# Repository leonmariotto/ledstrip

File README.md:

# Led Strip Project !

The goal here is to make a led strip controller board that just work.
Among other things the controller include a 3S battery and 4 potentiometer to control
RGBW independently.

The project layout is :
- hardware: kicad project to make the led strip controller board. Use KiCAD 9.
- cad: printable case for the controller + battery.
- software: software used to control the led strip. 
- ai: a setup to run CLI agent (codex) inside a docker with support for multiple AGENTS.md and support for KiMCP server.
- tools: tool to assist during development. Include KiMCP submodule.

## System requirements

- Must have a on/off switch
- Must have a battery properly scaled.
- Must provide a way to control color independently.
- Leds must be RGB with controllable intensity.
- Must provide a way to charge battery
- Must provide a way to program internal flash of MCU.
- Must be enclosed by a case.

## First board

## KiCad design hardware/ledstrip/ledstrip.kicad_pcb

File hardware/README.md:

# Hardware design for led strip controller !

## Hardware Requirements

- Must have a on/off switch
- Must provide a USB-C socket
- Must use a serie of Li-Ion battery along with a BMS
- Must use USB-C Power Delivery feature for efficient charging.
- Must use one potentiometer to control one color.
- Must provide an easy access to log via USB.
- Must support run while charging battery.
- Must provide protections against heating and short circuit.

## Ledstrip part !

Choosen RGBW ledstrip of 2 meters.
https://opencircuit.fr/produit/analog-rgbw-led-strip-rgb-plus-warm-white-60

## Hardware Architecture Design

So far the following components is identified :
- 3S Li-ion battery pack. 12V output.
- 3S BMS: off the shelf 3S (3-cells) BMS module. Shall support currents >
to expected (for 2 meter strip the expected current is 3.2A at 12V. So design it to 5-10A.
Start with an external BMS module, then progressively move into an integrated
BMS.
- USB-C connector
- USB to UART bridge (Silicon Labs CP2102(N), or FTDI FT230x or CH340)
- USB Power Delivery controller (ST STUSB4500) used to negociate high power input from USB.
- Battery charger IC (BQ25703A) : accept PD voltage and implement CC/CV.
Provide support for system load while charging.
- Buck regulator (12V to 3.3V) : integrated converter IC
- Logic-level N-MOSFETS x3, low RDS(on).
- Gate resistor / gate pull-down for each MOSFET, Fuse, ESD protections (TVS diodes, Schottky),
- Dedicated MIPI-10 connector for SWD.
- STM32G030K6 MCU.

### STM32G030K6 32-bit LQFP package

Use the following wiring :
- SWD: PA13, PA14, NRST
- UART: PA9 (TX), PA10 (RX)
- ADC (pots): PA0, PA1, PA2
- I2C to BQ25703A: PB6 (SCL), PB7 (SDA)
- PWM to MOSFET: PA8, PA6, PA7
- Power pins: VDD, VDDA, VSS, VSSA (decouple properly)
- BQ25703A_PROCHOT: PB9
- BQ25703A_CHRG_OK: PB9
Note that PWM need to use TIM1 for PA0 and TIM3 for PA6 and PA7 due to conflicts with UART.

## Building

A CI is here to build Gerber on a stable and reproducible environment.
PCBway is the recommended manufacturer.

## 4 layers

- Top (F.Cu): components + most routing (especially short local routes)
- Inner 1: solid GND plane (no splits)
- Inner 2: power pours (3.3 V, 12 V) + only necessary routing (prefer short, controlled routes)
- Bottom (B.Cu): routing + GND pour (stitched to Inner 1 often); use power pours only where it clearly helps (short distribution or local planes)

# TODO

- Create missing 3D view for footprint that lack it.
- MPN (Manufacturer Part Number) shall be included in the CI's BOM
- Generate Pick & Place (CPL/XY)
- Generate Plot Assembly Drwaing (Top/Bottom)

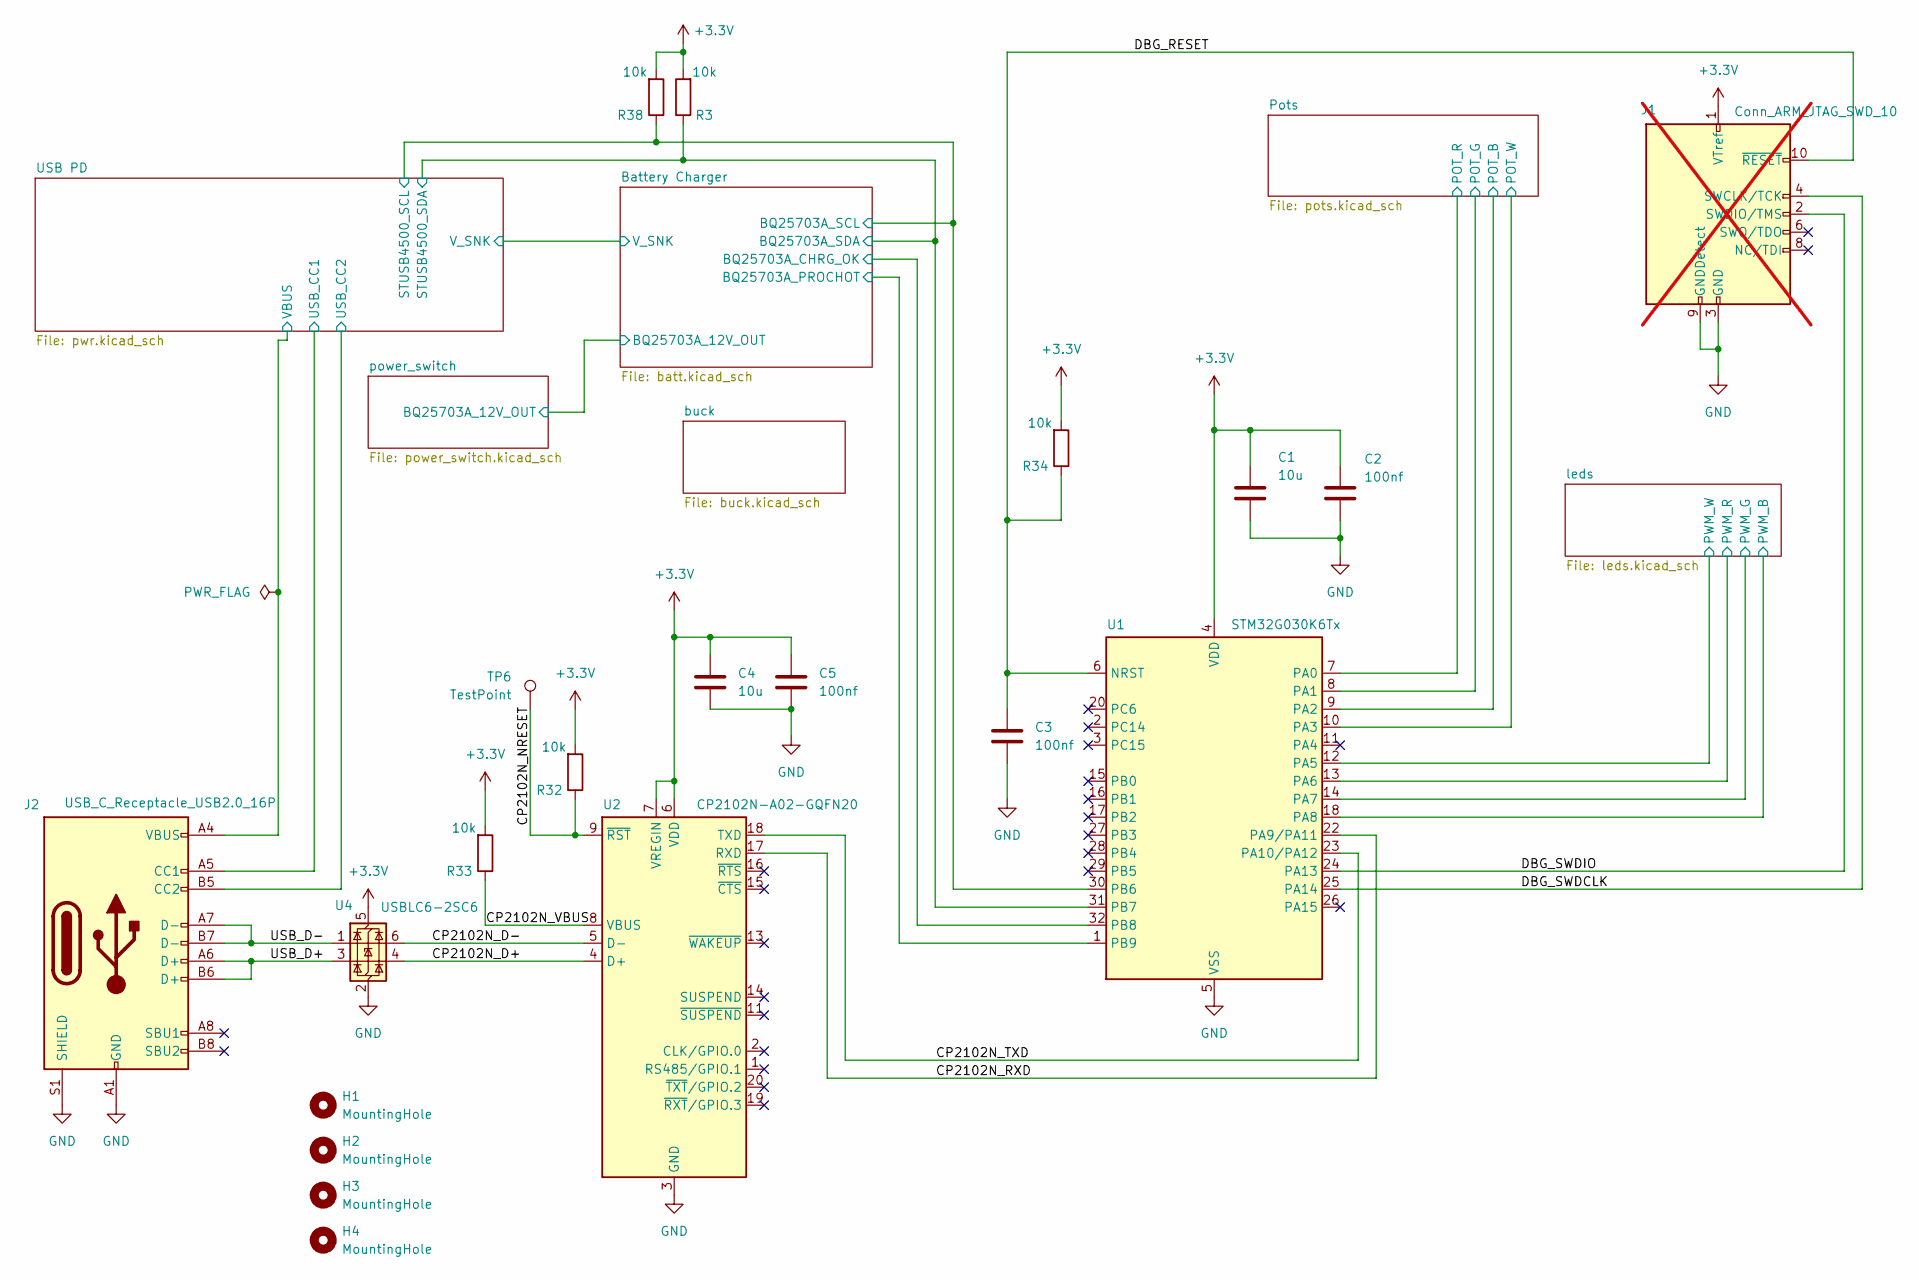
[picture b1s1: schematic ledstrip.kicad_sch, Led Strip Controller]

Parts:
C1, C4: 10u; C_0805_2012Metric; MPN CL21A106KAYNNN
C2, C3, C5: 100nf; C_0603_1608Metric; MPN CL10B104KA8VPJC
H1, H2, H3, H4: MountingHole; MountingHole_3.2mm_M3
J1: Conn_ARM_JTAG_SWD_10; PinHeader_2x05_P1.27mm_Vertical; not fitted
J2: USB_C_Receptacle_USB2.0_16P; USB_C_Receptacle_GCT_USB4105-xx-A_16P_TopMnt_Horizontal_PRO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; MPN USB4105-GF-A-060
R3, R32, R33, R34, R38: 10k; R_0805_2012Metric; MPN MCU0805MD1002BP500
TP6: TestPoint; TestPoint_Pad_1.0x1.0mm
U1: STM32G030K6Tx; LQFP-32_7x7mm_P0.8mm; MPN STM32G030K6T6
U2: CP2102N-A02-GQFN20; SiliconLabs_QFN-20-1EP_3x3mm_P0.5mm_EP1.8x1.8mm; MPN CP2102N-A02-GQFN20
U4: USBLC6-2SC6; SOT-23-6; MPN USBLC6-2SC6

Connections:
+3.3V: C1.1, C2.1, C4.1, C5.1, J1.1 (VTref), R3.2, R32.2, R33.2, R34.2, R38.2, U1.4 (VDD), U2.6 (VDD), U2.7 (VREGIN), U4.5 (VBUS); also elsewhere on the board
/Battery Charger/BQ25703A_CHRG_OK: U1.32 (PB8); also elsewhere on the board
/Battery Charger/BQ25703A_PROCHOT: U1.1 (PB9); also elsewhere on the board
/Battery Charger/BQ25703A_SCL: R38.1, U1.30 (PB6); also elsewhere on the board
/Battery Charger/BQ25703A_SDA: R3.1, U1.31 (PB7); also elsewhere on the board
/CP2102N_D+: U2.4 (D+), U4.4 (I/O2)
/CP2102N_D-: U2.5 (D-), U4.6 (I/O1)
/CP2102N_NRESET: R32.1, TP6.1, U2.9 (~RST)
/CP2102N_RXD: U1.22 (PA9/PA11), U2.17 (RXD)
/CP2102N_TXD: U1.23 (PA10/PA12), U2.18 (TXD)
/CP2102N_VBUS: R33.1, U2.8 (VBUS)
/DBG_RESET: C3.1, J1.10 (~RESET), R34.1, U1.6 (NRST)
/DBG_SWDCLK: J1.4 (SWCLK/TCK), U1.25 (PA14)
/DBG_SWDIO: J1.2 (SWDIO/TMS), U1.24 (PA13)
/Pots/POT_B: U1.9 (PA2); also elsewhere on the board
/Pots/POT_G: U1.8 (PA1); also elsewhere on the board
/Pots/POT_R: U1.7 (PA0); also elsewhere on the board
/Pots/POT_W: U1.10 (PA3); also elsewhere on the board
/USB PD/USB_CC1: J2.A5 (CC1); also elsewhere on the board
/USB PD/USB_CC2: J2.B5 (CC2); also elsewhere on the board
/USB PD/VBUS: J2.A4 (VBUS), J2.A9 (VBUS), J2.B4 (VBUS), J2.B9 (VBUS); also elsewhere on the board
/USB_D+: J2.A6 (D+), J2.B6 (D+), U4.3 (I/O2)
/USB_D-: J2.A7 (D-), J2.B7 (D-), U4.1 (I/O1)
/leds/PWM_B: U1.18 (PA8); also elsewhere on the board
/leds/PWM_G: U1.14 (PA7); also elsewhere on the board
/leds/PWM_R: U1.13 (PA6); also elsewhere on the board
/leds/PWM_W: U1.12 (PA5); also elsewhere on the board
GND: C1.2, C2.2, C3.2, C4.2, C5.2, J1.3 (GND), J1.5 (GND), J1.9 (GNDDetect), J2.A1 (GND), J2.A12 (GND), J2.B1 (GND), J2.B12 (GND), J2.S1 (SHIELD), U1.5 (VSS), U2.3 (GND), U2.12 (GND), U2.21 (GND), U4.2 (GND); also elsewhere on the board

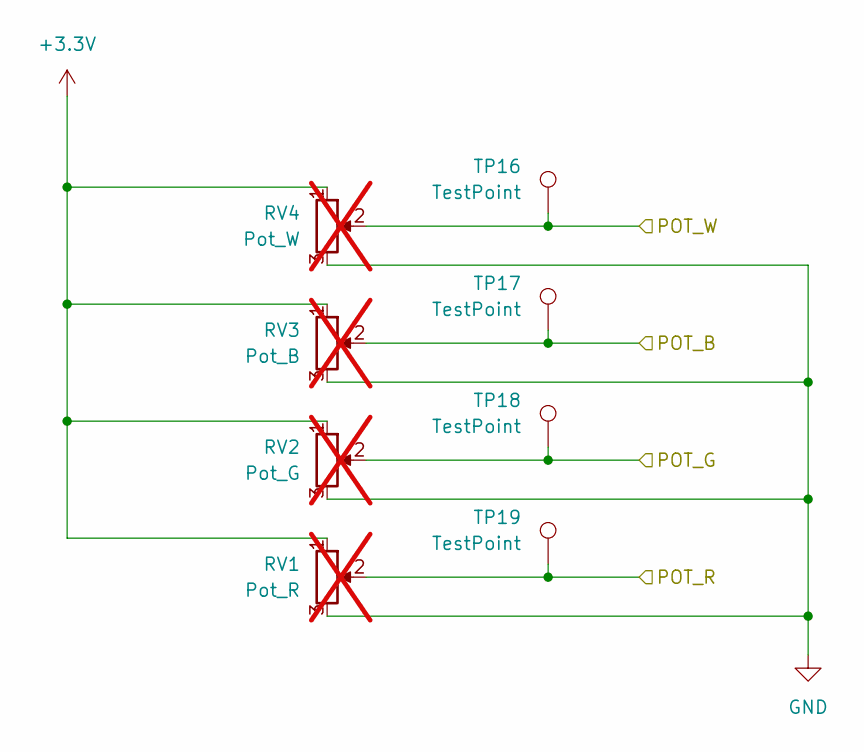
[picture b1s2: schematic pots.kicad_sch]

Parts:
RV1: Pot_R; Potentiometer_Bourns_PTV09A-1_Single_Vertical; MPN PTV09A-6030U-B103; not fitted
RV2: Pot_G; Potentiometer_Bourns_PTV09A-1_Single_Vertical; MPN PTV09A-6030U-B103; not fitted
RV3: Pot_B; Potentiometer_Bourns_PTV09A-1_Single_Vertical; MPN PTV09A-6030U-B103; not fitted
RV4: Pot_W; Potentiometer_Bourns_PTV09A-1_Single_Vertical; MPN PTV09A-6030U-B103; not fitted
TP16, TP17, TP18, TP19: TestPoint; TestPoint_Pad_1.0x1.0mm

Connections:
+3.3V: RV1.1, RV2.1, RV3.1, RV4.1; also elsewhere on the board
/Pots/POT_B: RV3.2, TP17.1; also elsewhere on the board
/Pots/POT_G: RV2.2, TP18.1; also elsewhere on the board
/Pots/POT_R: RV1.2, TP19.1; also elsewhere on the board
/Pots/POT_W: RV4.2, TP16.1; also elsewhere on the board
GND: RV1.3, RV2.3, RV3.3, RV4.3; also elsewhere on the board

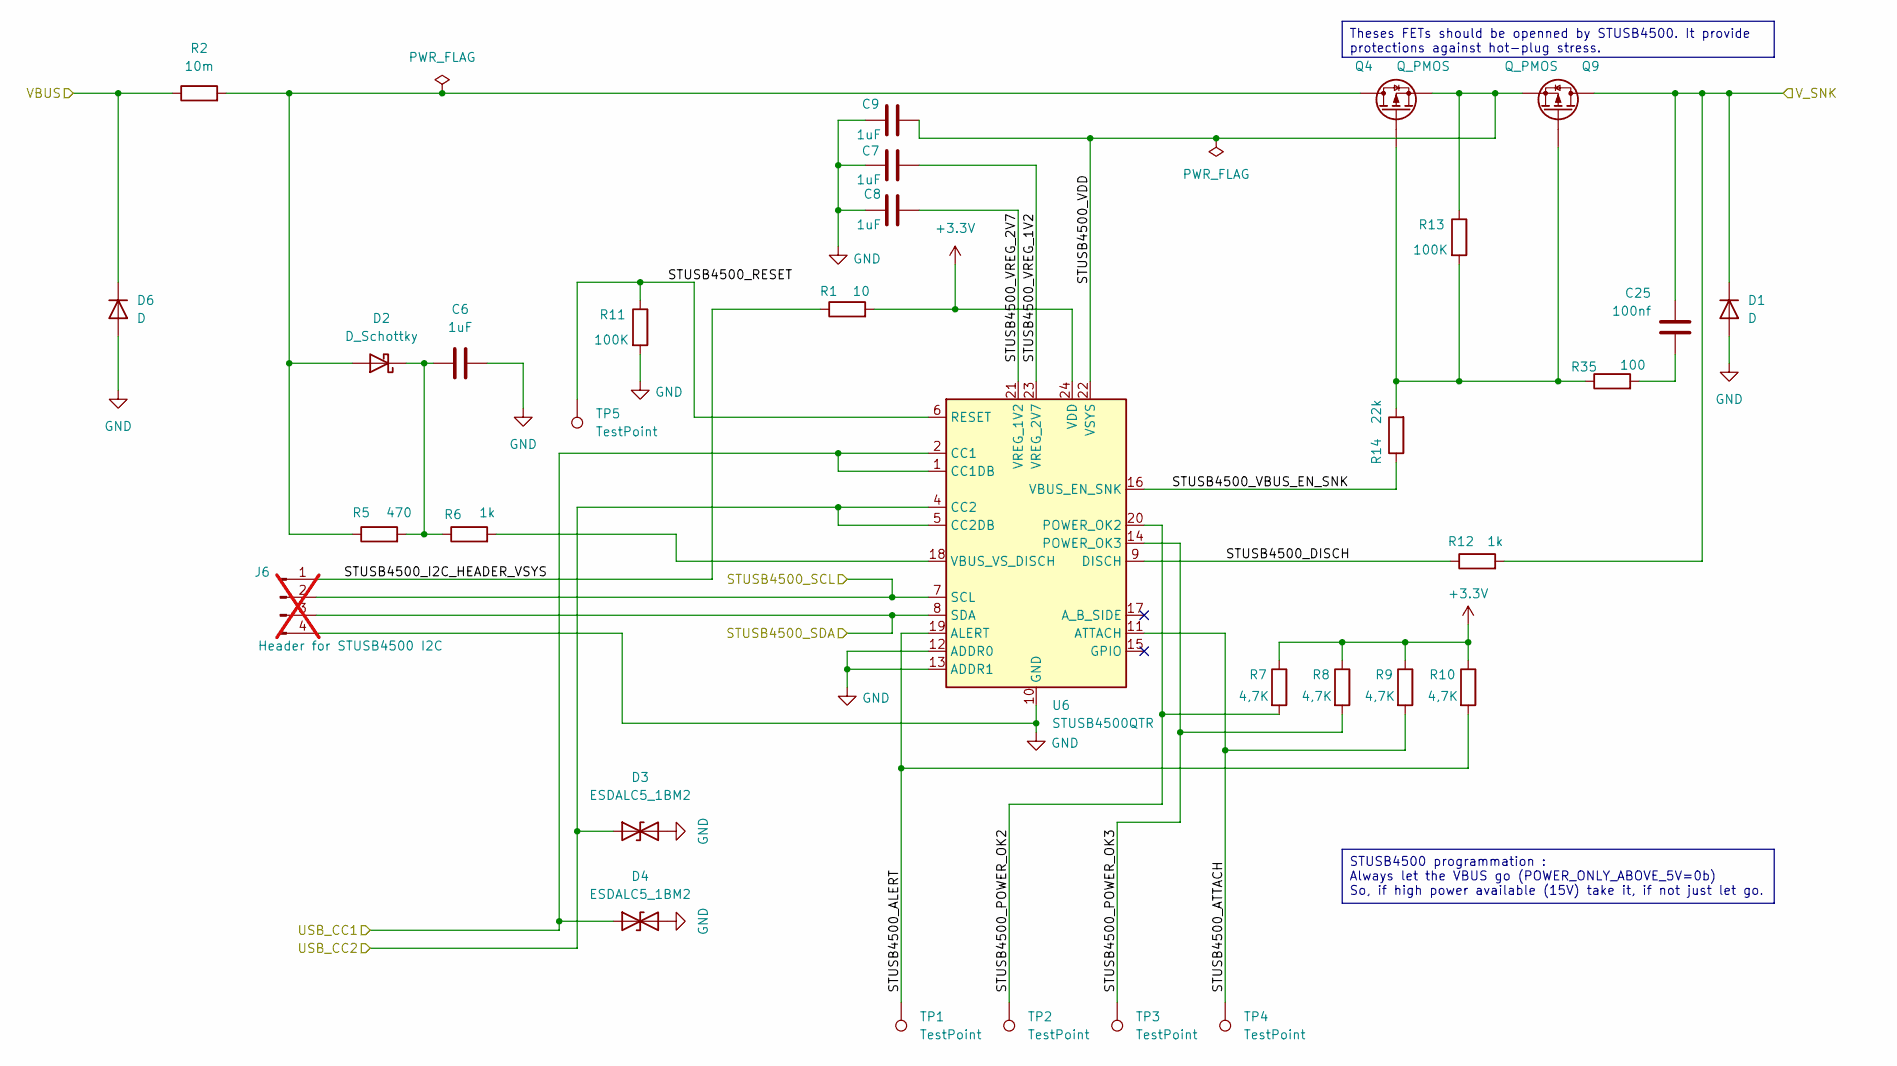
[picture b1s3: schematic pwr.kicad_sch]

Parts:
C6, C7, C8, C9: 1uF; C_0603_1608Metric; MPN 885012106022
C25: 100nf; C_0603_1608Metric; MPN CL10B104KA8VPJC
D1: D; D_0603_1608Metric; MPN ESDA20P50-1U1M
D2: D_Schottky; D_SOD-323; MPN BAT54JFILM
D3, D4: ESDALC5_1BM2; D_SOD-882; MPN ESDALC5-1BT2
D6: D; D_SMA; MPN SMAJ15AHM3_A-H
J6: Header for STUSB4500 I2C; PinHeader_1x04_P2.54mm_Vertical; not fitted
Q4, Q9: Q_PMOS; POWERFLAT_3P3X3P3_STM; MPN STL6P3LLH6
R1: 10; R_0805_2012Metric; MPN CRCW080510R0JNEAHP
R2: 10m; R_0805_2012Metric; MPN WSLP0805R0100DEA
R5: 470; R_0603_1608Metric; MPN SFR03EZPJ471
R6, R12: 1k; R_0603_1608Metric; MPN RCA06031K00FKEAHP
R7, R8, R9, R10: 4,7K; R_0805_2012Metric; MPN ERA-6ARW472V
R11, R13: 100K; R_0805_2012Metric; MPN RT0805BRB07100KL
R14: 22k; R_0805_2012Metric; MPN MCU08050C2202FP500
R35: 100; R_0805_2012Metric; MPN RP0805CT-1000GN-96TR
TP1, TP2, TP3, TP4, TP5: TestPoint; TestPoint_Pad_1.0x1.0mm
U6: STUSB4500QTR; QFN-24-1EP_4x4mm_P0.5mm_EP2.7x2.7mm; MPN STUSB4500QTR

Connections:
+3.3V: R1.2, R7.1, R8.1, R9.1, R10.1, U6.24 (VDD); also elsewhere on the board
/Battery Charger/BQ25703A_SCL: J6.2, U6.7 (SCL); also elsewhere on the board
/Battery Charger/BQ25703A_SDA: J6.3, U6.8 (SDA); also elsewhere on the board
/Battery Charger/V_SNK: C25.1, D1.1 (K), Q9.D, R12.2; also elsewhere on the board
/USB PD/STUSB4500_ALERT: R10.2, TP1.1, U6.19 (ALERT)
/USB PD/STUSB4500_ATTACH: R9.2, TP4.1, U6.11 (ATTACH)
/USB PD/STUSB4500_DISCH: R12.1, U6.9 (DISCH)
/USB PD/STUSB4500_I2C_HEADER_VSYS: J6.1, R1.1
/USB PD/STUSB4500_POWER_OK2: R7.2, TP2.1, U6.20 (POWER_OK2)
/USB PD/STUSB4500_POWER_OK3: R8.2, TP3.1, U6.14 (POWER_OK3)
/USB PD/STUSB4500_RESET: R11.1, TP5.1, U6.6 (RESET)
/USB PD/STUSB4500_VBUS_EN_SNK: R14.1, U6.16 (VBUS_EN_SNK)
/USB PD/STUSB4500_VDD: C9.2, Q4.S, Q9.S, R13.1, U6.22 (VSYS)
/USB PD/STUSB4500_VREG_1V2: C7.1, U6.23 (VREG_2V7)
/USB PD/STUSB4500_VREG_2V7: C8.1, U6.21 (VREG_1V2)
/USB PD/USB_CC1: D4.1 (A1), U6.1 (CC1DB), U6.2 (CC1); also elsewhere on the board
/USB PD/USB_CC2: D3.1 (A1), U6.4 (CC2), U6.5 (CC2DB); also elsewhere on the board
/USB PD/VBUS: D6.1 (K), R2.1; also elsewhere on the board
GND: C6.2, C7.2, C8.2, C9.1, D1.2 (A), D3.2 (A2), D4.2 (A2), D6.2 (A), J6.4, R11.2, U6.10 (GND), U6.12 (ADDR0), U6.13 (ADDR1), U6.25 (GND); also elsewhere on the board
unnamed: C25.2, R35.2
unnamed: D2.2 (A), Q4.D, R2.2, R5.1
unnamed: C6.1, D2.1 (K), R5.2, R6.1
unnamed: Q4.G, Q9.G, R13.2, R14.2, R35.1
unnamed: R6.2, U6.18 (VBUS_VS_DISCH)

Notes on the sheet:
Theses FETs should be openned by STUSB4500. It provide protections against hot-plug stress.
STUSB4500 programmation : Always let the VBUS go (POWER_ONLY_ABOVE_5V=0b) So, if high power available (15V) take it, if not just let go.

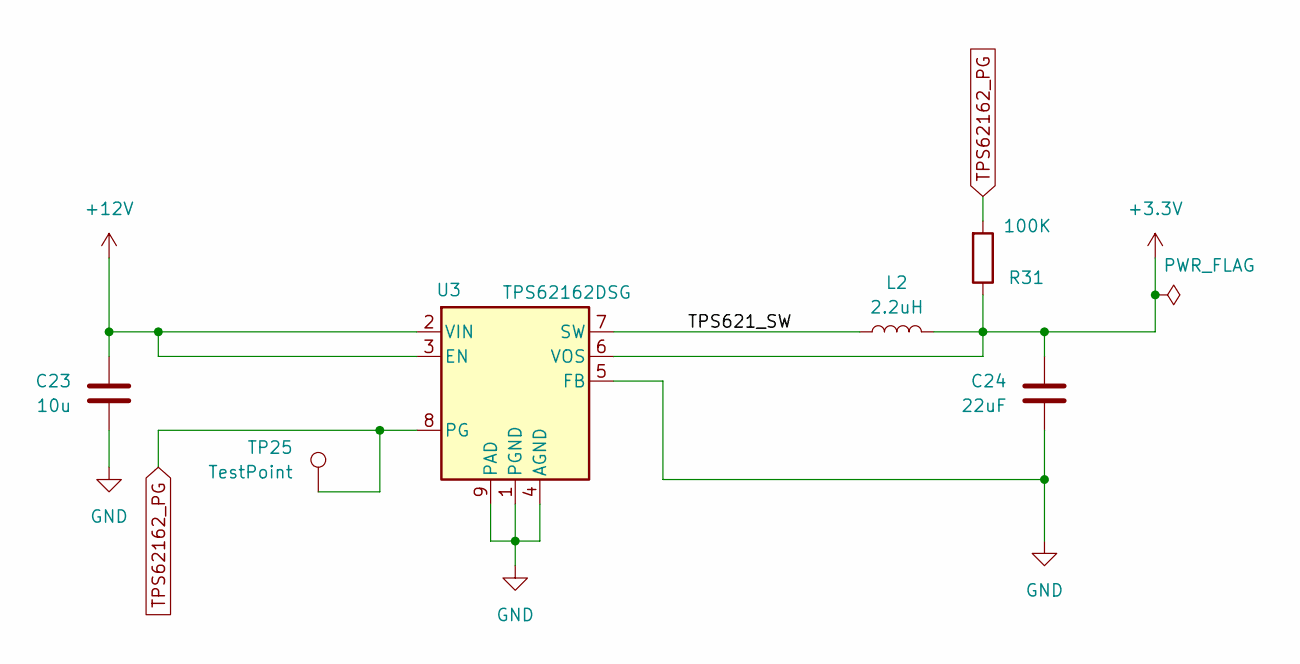
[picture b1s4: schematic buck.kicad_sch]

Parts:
C23: 10u; C_0805_2012Metric; MPN CL21A106KAYNNN
C24: 22uF; C_0603_1608Metric; MPN CL10Z226MS96PNC
L2: 2.2uH; L_1206_3216Metric; MPN PFL3215-222MEC
R31: 100K; R_0805_2012Metric; MPN RT0805BRB07100KL
TP25: TestPoint; TestPoint_Pad_1.0x1.0mm
U3: TPS62162DSG; WSON-8-1EP_2x2mm_P0.5mm_EP0.9x1.6mm_ThermalVias; MPN TPS62162DSGT

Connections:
+3.3V: C24.1, L2.2, R31.1, U3.6 (VOS); also elsewhere on the board
+12V: C23.1, U3.2 (VIN), U3.3 (EN); also elsewhere on the board
/buck/TPS621_SW: L2.1, U3.7 (SW)
GND: C23.2, C24.2, U3.1 (PGND), U3.4 (AGND), U3.5 (FB), U3.9 (PAD); also elsewhere on the board
TPS62162_PG: R31.2, TP25.1, U3.8 (PG)

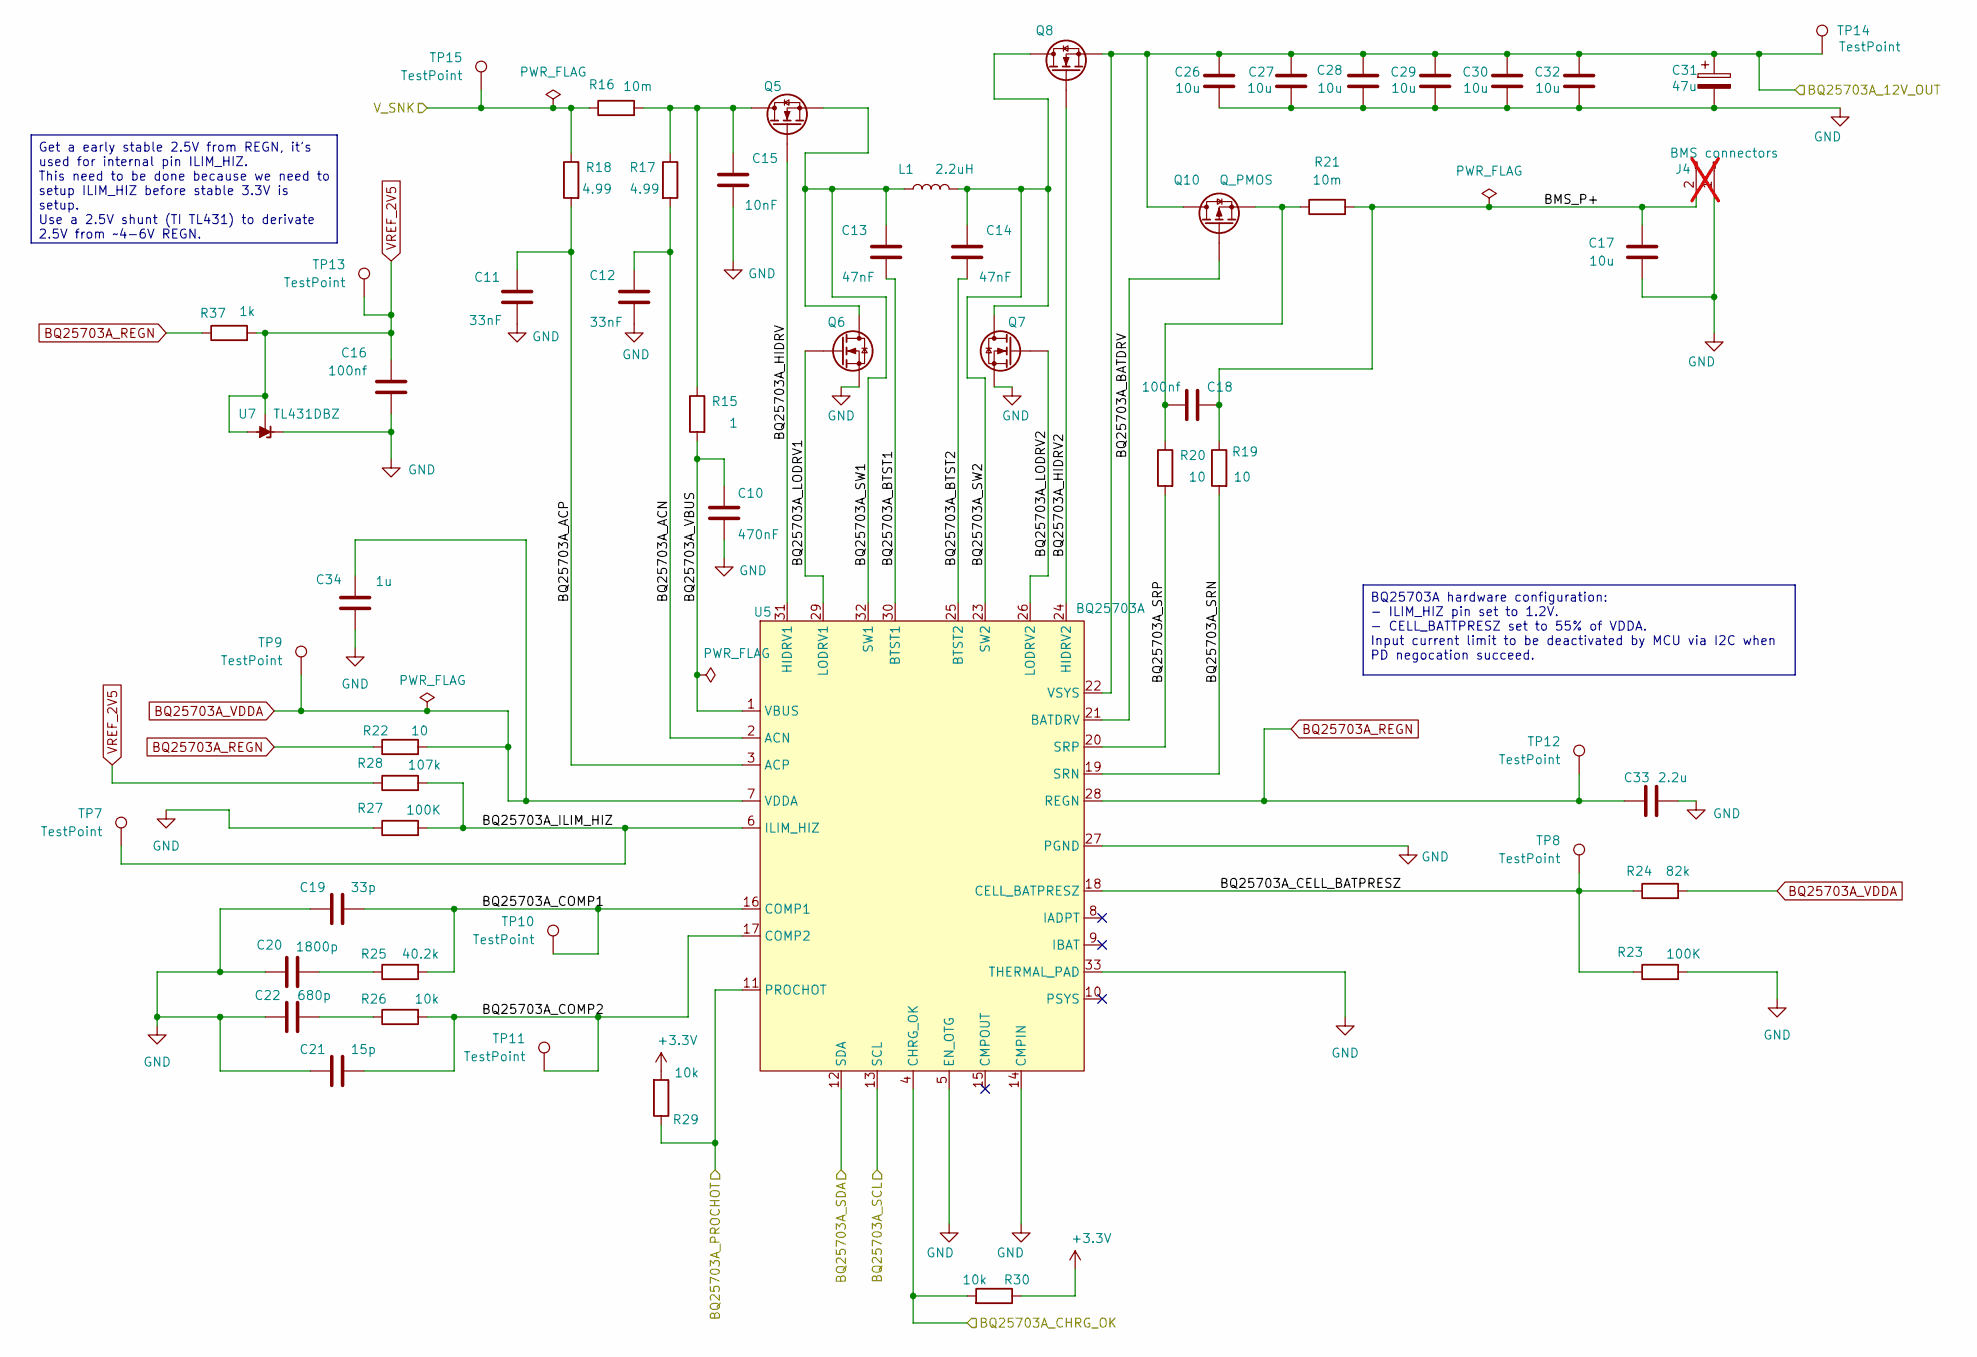
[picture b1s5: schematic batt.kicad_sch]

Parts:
C10: 470nF; C_0603_1608Metric; MPN C0603C474J3RACTU
C11, C12: 33nF; C_0603_1608Metric; MPN 06031C333KAT2A
C13, C14: 47nF; C_0603_1608Metric; MPN KGM15AR51V473KT
C15: 10nF; C_0603_1608Metric; MPN 03028-BR103YKU-J
C16, C18: 100nf; C_0603_1608Metric; MPN CL10B104KA8VPJC
C17, C26, C27, C28, C29, C30, C32: 10u; C_0805_2012Metric; MPN CL21A106KAYNNN
C19: 33p; C_0603_1608Metric; MPN KGQ15ACG2A330GT
C20: 1800p; C_0603_1608Metric; MPN VJ0603Y182JXAAC
C21: 15p; C_0603_1608Metric; MPN 06031U150JAT2A
C22: 680p; C_0603_1608Metric; MPN VJ0603A681GXAAC
C31: 47u; CP_EIA-7343-20_Kemet-V; MPN 20TQC47MYF
C33: 2.2u; C_0603_1608Metric; MPN CL03A225MO5C65C
C34: 1u; C_0603_1608Metric; MPN AMK063AC6105MP-F
J4: BMS connectors; PinHeader_1x02_P2.54mm_Vertical; not fitted
L1: 2.2uH; L_Wurth_WE-LHMI-8030_9.7x8.5mm; MPN 74437356022
Q5, Q6, Q7, Q8: Q_NMOS; VSON-8_3.3x3.3mm_P0.65mm_NexFET; MPN CSD17551Q3A
Q10: Q_PMOS; POWERFLAT_3P3X3P3_STM; MPN STL6P3LLH6
R15: 1; R_0805_2012Metric; MPN AC0805FR-071RL
R16, R21: 10m; R_0805_2012Metric; MPN WSLP0805R0100DEA
R17, R18: 4.99; R_0805_2012Metric; MPN CRCW08054R99DKEAHP
R19, R20: 10; R_0805_2012Metric; MPN MCU0805MC1009FP500
R22: 10; R_0805_2012Metric; MPN CRCW080510R0JNEAHP
R23, R27: 100K; R_0805_2012Metric; MPN RT0805BRB07100KL
R24: 82k; R_0805_2012Metric; MPN ERA-6ARB823V
R25: 40.2k; R_0805_2012Metric; MPN PHP00805E40R2BST1
R26, R29, R30: 10k; R_0805_2012Metric; MPN MCU0805MD1002BP500
R28: 107k; R_0805_2012Metric; MPN CRCW0805107KFKEA
R37: 1k; R_0603_1608Metric; MPN RCA06031K00FKEAHP
TP7, TP8, TP9, TP10, TP11, TP12, TP13, TP14, TP15: TestPoint; TestPoint_Pad_1.0x1.0mm
U5: BQ25703A; Texas_RSN_WQFN-32-1EP_4x4mm_P0.4mm_EP2.8x2.8mm_ThermalVias; MPN BQ25703ARSNR
U7: TL431DBZ; SOT-23; MPN TL431AQDBZR

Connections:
+3.3V: R29.2, R30.1; also elsewhere on the board
/Battery Charger/BMS_P+: C17.1, C18.2, J4.2, R19.1, R21.2
/Battery Charger/BQ25703A_12V_OUT: C26.1, C27.1, C28.1, C29.1, C30.1, C31.1, C32.1, Q8.S, Q10.D, TP14.1, U5.22 (VSYS); also elsewhere on the board
/Battery Charger/BQ25703A_ACN: C12.2, R17.2, U5.2 (ACN)
/Battery Charger/BQ25703A_ACP: C11.2, R18.2, U5.3 (ACP)
/Battery Charger/BQ25703A_BATDRV: Q10.G, U5.21 (BATDRV)
/Battery Charger/BQ25703A_BTST1: C13.1, U5.30 (BTST1)
/Battery Charger/BQ25703A_BTST2: C14.1, U5.25 (BTST2)
/Battery Charger/BQ25703A_CELL_BATPRESZ: R23.1, R24.1, TP8.1, U5.18 (CELL_BATPRESZ)
/Battery Charger/BQ25703A_CHRG_OK: R30.2, U5.4 (CHRG_OK); also elsewhere on the board
/Battery Charger/BQ25703A_COMP1: C19.1, R25.2, TP10.1, U5.16 (COMP1)
/Battery Charger/BQ25703A_COMP2: C21.1, R26.2, TP11.1, U5.17 (COMP2)
/Battery Charger/BQ25703A_HIDRV: Q5.G, U5.31 (HIDRV1)
/Battery Charger/BQ25703A_HIDRV2: Q8.G, U5.24 (HIDRV2)
/Battery Charger/BQ25703A_ILIM_HIZ: R27.2, R28.2, TP7.1, U5.6 (ILIM_HIZ)
/Battery Charger/BQ25703A_LODRV1: Q6.G, U5.29 (LODRV1)
/Battery Charger/BQ25703A_LODRV2: Q7.G, U5.26 (LODRV2)
/Battery Charger/BQ25703A_PROCHOT: R29.1, U5.11 (PROCHOT); also elsewhere on the board
/Battery Charger/BQ25703A_SCL: U5.13 (SCL); also elsewhere on the board
/Battery Charger/BQ25703A_SDA: U5.12 (SDA); also elsewhere on the board
/Battery Charger/BQ25703A_SRN: R19.2, U5.19 (SRN)
/Battery Charger/BQ25703A_SRP: R20.2, U5.20 (SRP)
/Battery Charger/BQ25703A_SW1: C13.2, L1.1, Q5.S, Q6.D, U5.32 (SW1)
/Battery Charger/BQ25703A_SW2: C14.2, L1.2, Q7.D, Q8.D, U5.23 (SW2)
/Battery Charger/BQ25703A_VBUS: C10.2, R15.2, U5.1 (VBUS)
/Battery Charger/V_SNK: R16.1, R18.1, TP15.1; also elsewhere on the board
BQ25703A_REGN: C33.1, R22.1, R37.1, TP12.1, U5.28 (REGN)
BQ25703A_VDDA: C34.1, R22.2, R24.2, TP9.1, U5.7 (VDDA)
GND: C10.1, C11.1, C12.1, C15.1, C16.2, C17.2, C19.2, C20.2, C21.2, C22.2, C26.2, C27.2, C28.2, C29.2, C30.2, C31.2, C32.2, C33.2, C34.2, J4.1, Q6.S, Q7.S, R23.2, R27.1, U5.5 (EN_OTG), U5.14 (CMPIN), U5.27 (PGND), U5.33 (THERMAL_PAD), U7.1 (K); also elsewhere on the board
unnamed: C15.2, Q5.D, R15.1, R16.2, R17.1
unnamed: C18.1, Q10.S, R20.1, R21.1
unnamed: C20.1, R25.1
unnamed: C22.1, R26.1
VREF_2V5: C16.1, R28.1, R37.2, TP13.1, U7.2 (REF), U7.3 (A)

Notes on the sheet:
Get a early stable 2.5V from REGN, it's used for internal pin ILIM_HIZ. This need to be done because we need to setup ILIM_HIZ before stable 3.3V is setup. Use a 2.5V shunt (TI TL431) to derivate 2.5V from ~4-6V REGN.
BQ25703A hardware configuration: - ILIM_HIZ pin set to 1.2V. - CELL_BATTPRESZ set to 55% of VDDA. Input current limit to be deactivated by MCU via I2C when PD negocation succeed.

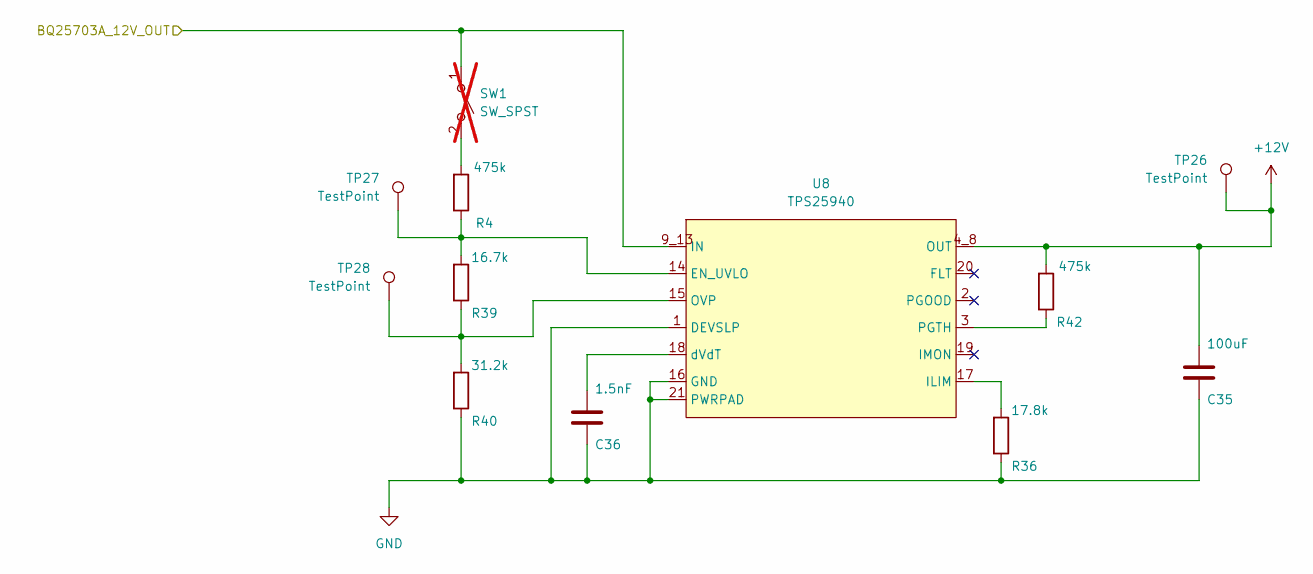
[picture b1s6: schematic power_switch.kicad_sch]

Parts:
C35: 100uF; C_1210_3225Metric; MPN MLASE32MAB5107MPNA01
C36: 1.5nF; C_0603_1608Metric; MPN GRT033R61A152KE01D
R4, R42: 475k; R_0805_2012Metric; MPN CRCW0805475KFHEAP
R36: 17.8k; R_0805_2012Metric; MPN TNPW080517K8BETY
R39: 16.7k; R_0805_2012Metric; MPN TNPW080516K7BEEN
R40: 31.2k; R_0805_2012Metric; MPN TNPW080531K2BEEN
SW1: SW_SPST; PinHeader_1x02_P2.54mm_Vertical; MPN SW3001A; not fitted
TP26, TP27, TP28: TestPoint; TestPoint_Pad_1.0x1.0mm
U8: TPS25940; QFN-20-1EP_3x4mm_P0.5mm_EP1.65x2.65mm_ThermalVias_PROJECTCO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; MPN TPS25940ARVCT

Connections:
+12V: C35.1, R42.2, TP26.1, U8.4_8 (OUT); also elsewhere on the board
/Battery Charger/BQ25703A_12V_OUT: SW1.1 (A), U8.9_13 (IN); also elsewhere on the board
GND: C35.2, C36.2, R36.1, R40.1, U8.1 (DEVSLP), U8.16 (GND), U8.21 (PWRPAD); also elsewhere on the board
unnamed: R4.2, SW1.2 (B)
unnamed: R4.1, R39.2, TP27.1, U8.14 (EN_UVLO)
unnamed: R36.2, U8.17 (ILIM)
unnamed: R39.1, R40.2, TP28.1, U8.15 (OVP)
unnamed: R42.1, U8.3 (PGTH)
unnamed: C36.1, U8.18 (dVdT)

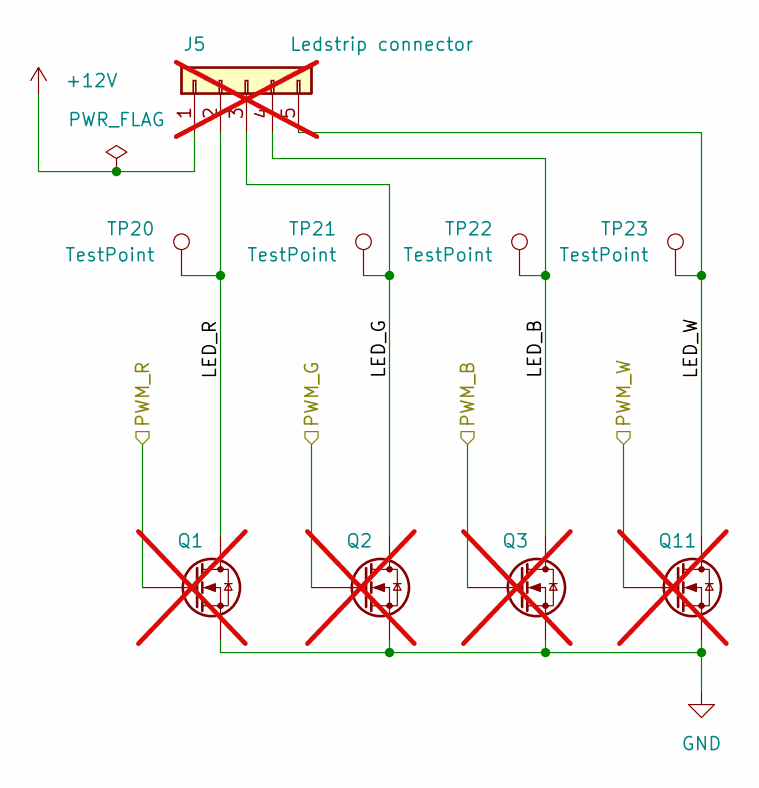
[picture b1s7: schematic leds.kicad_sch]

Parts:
J5: Ledstrip connector; JST_XH_S5B-XH-A_1x05_P2.50mm_Horizontal; MPN S5B-XH-A-1(LF)(SN); not fitted
Q1, Q2, Q3, Q11: Q_NMOS; TO-220-3_Vertical; MPN IRL3705NPBF; not fitted
TP20, TP21, TP22, TP23: TestPoint; TestPoint_Pad_1.0x1.0mm

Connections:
+12V: J5.1; also elsewhere on the board
/leds/LED_B: J5.4, Q3.D, TP22.1
/leds/LED_G: J5.3, Q2.D, TP21.1
/leds/LED_R: J5.2, Q1.D, TP20.1
/leds/LED_W: J5.5, Q11.D, TP23.1
/leds/PWM_B: Q3.G; also elsewhere on the board
/leds/PWM_G: Q2.G; also elsewhere on the board
/leds/PWM_R: Q1.G; also elsewhere on the board
/leds/PWM_W: Q11.G; also elsewhere on the board
GND: Q1.S, Q2.S, Q3.S, Q11.S; also elsewhere on the board

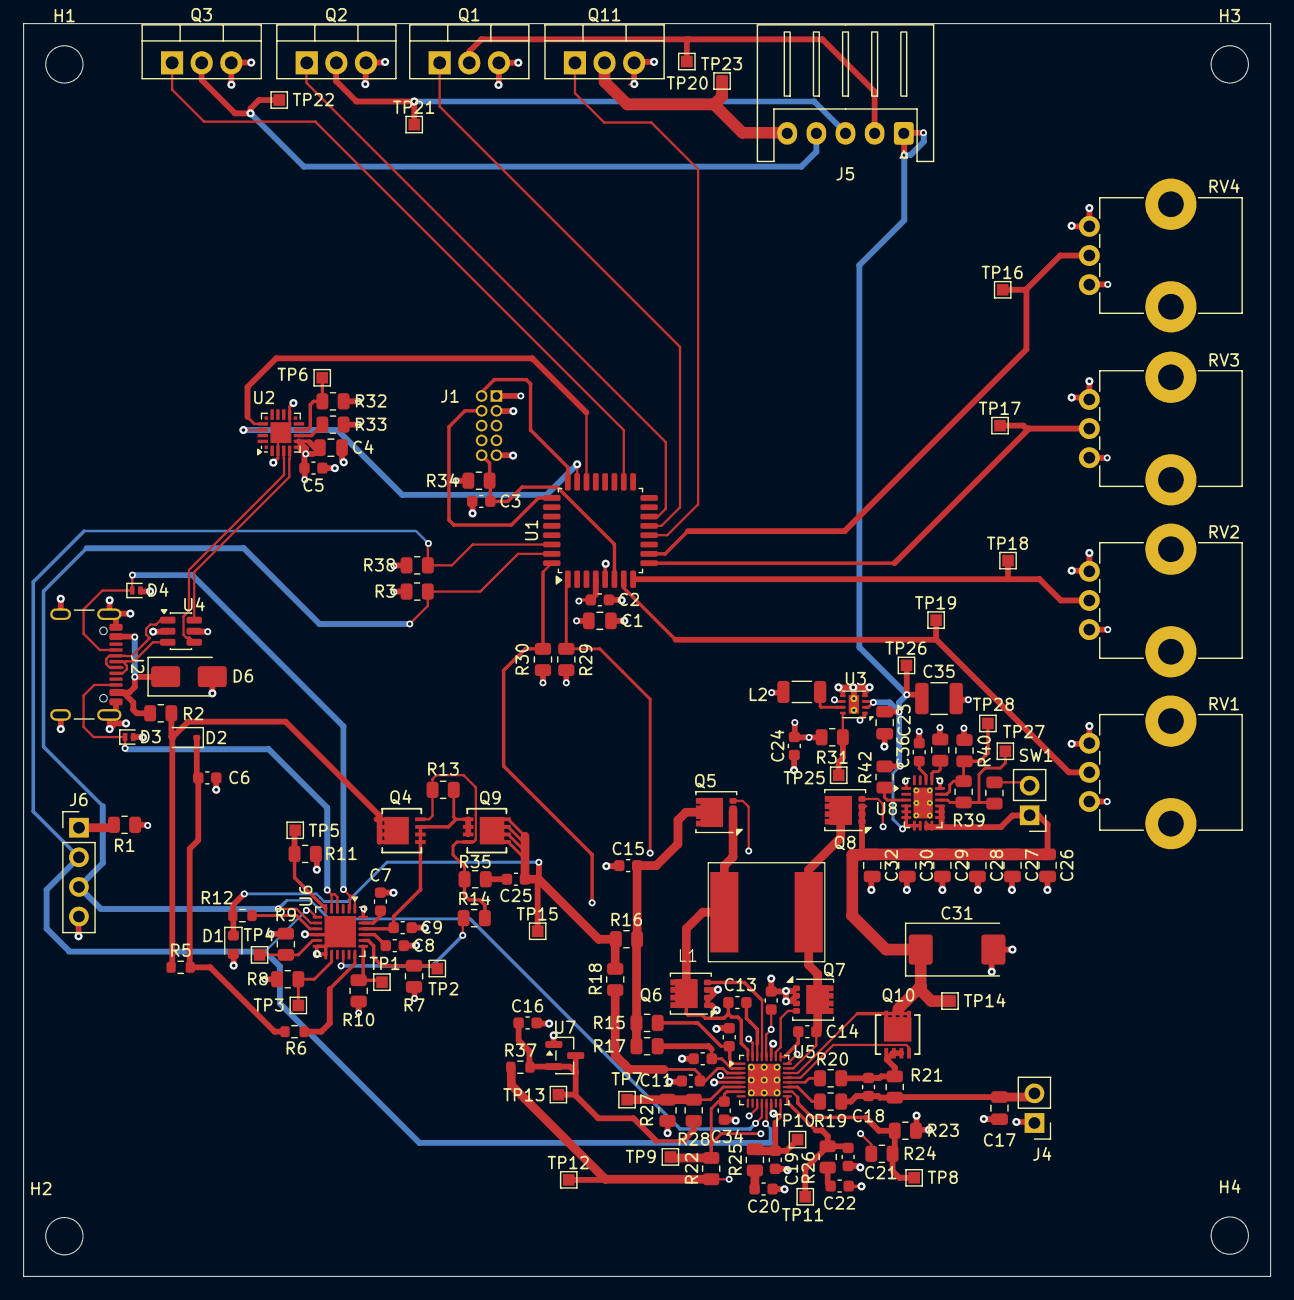
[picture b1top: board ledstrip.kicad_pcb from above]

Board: 4 copper layers, 107.0 x 107.5 mm, 144 parts (1 on the bottom side), 85 nets.

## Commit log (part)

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2025-11-13 First !
2025-11-15 Add hardware design documents.
2025-11-16 Start kicad project, shcematics ongoing
    MCU integrated
    Still need to do power path
2025-11-16 Update drawio
2025-11-20 Minor improvements, add I2C header for STUSB4500
2025-11-23 Update documentation, add mfor software and CAD
2025-11-23 Add TVS on CC lines, select a footprint for resistors.
2025-11-26 Update part list
2025-11-30 Sheet rework, new symbols
    Create and add symbol for BQ25703N
    Add symbol for BMS interface
    Add symbol for LED strip socket
    Move power management related things into sub-sheet.
2025-11-30 Do ERC with github actions.
2025-11-30 Fix artifact location for ERC reports
2025-11-30 Update doc, TODOs
2025-11-30 Select part and add potentiometers to schematics.
2025-11-30 Update TODO
2025-12-02 Add TVS diode on VBUS line, improve STUSB4500 integration
    Add P-MOSFET controled by STUSB4500 on VBUS line
2025-12-06 Add STL6P3LLH6 sym from ulra librarian, add a TODO_plan_for_this_weekend.md for project organization
2025-12-06 Finished STUSB4500 integration.
    Improved BQ25703A integration.
    Created a footprint for Wurth inductance.
2025-12-06 Splitted into multiple sheets.
    BQ25703A integrated
    buck converter OK
2025-12-07 Fix ERC errors.
2025-12-07 Start a setup to use generative AI in this project.
2025-12-07 AI setup OK.
    Agent is able to parse schematics and verify many things.
2025-12-07 Fix last errors in schematics
    Missing footprint, missing distributor link.
    Updated project sym-lib-table for ERC checks.
2025-12-07 Remove backup files.
2025-12-07 Update work progress for today
2025-12-07 Upload a review of STUSB4500 integration, TODO
2025-12-07 Update TODOs
2025-12-09 Add label on nodes.
2025-12-09 Added a pull down to VSYS
    (external powered if header connected, otherwise VSYS is tied to GND) in STUSB4500 integration.
2025-12-13 Update READMEs
    Choose a manufacturer for the board
    Add some part list : battery pack, external BMS
2025-12-13 Install ripgrep as codex want to use it.
2025-12-13 Start PCB design !
    Use 4 layers.
    Global options set for PCBWay manufacturer.
2025-12-14 Continue PCB.
    Create netlists and color them.
    Fix wrong symbol pin <-> foot print pins mapping.
    Replace footprint and part for leds N-MOSFET.
2025-12-14 Fix ERC warnings.
2025-12-26 Fix ILIM_HIZ setting on BQ25703A
    Add comments on schematics about hardware configuration.
    Setup a early stable 2.5V from REGN to setup ILIM_HIZ correctly.
2025-12-26 Wire STUSB4500 I2C to MCU
2026-01-03 Add KiMCP submodule.
2026-01-03 Fix KiMCP, connect it to Codex.
2026-01-08 Fix ERC errors
2026-01-20 Improve footprint placements.
2026-01-20 Launch KiMCP server along with codex.
2026-01-22 Improve slightly placements.
    Add next step in README.md.
    Add description of layers usages.
2026-01-31 Added GND zone in L2 layer + vias for ground.
2026-01-31 Add 3.3V and 12V zones on L3, add vias.
2026-02-01 Start editing some trace.
2026-02-08 All signal tracks done, PCB almost terminated
    Only GND, 3.3V and 12V pins-to-via tracks left.
2026-02-27 Add ON/OFF button to PCB.
    Decrease power zone size.
2026-02-27 Update docs.
2026-02-27 Remove power zones, use tracks instead.
2026-02-27 Update board parameter, try to reduce DRC errors.
2026-02-28 Fix DRC errors
    Reduce globa;l solder mask clearance based on PCBWay limitations
    Fix POWERFLAT_3P3X3P3_STM footprint.
2026-02-28 Fix all DRC errors.
2026-02-28 Enable DRC and Export job in CI.
2026-02-28 Fix workflow file.
2026-02-28 Fix ERC and DRC errors.
    Use a custom copy of USB-C in project library to avoid having a version
    mismatch with CI.
    Fix QFN-20-1EP_3x4mm_P0.5mm_EP1.65x2.65mm_ThermalVias mismatch pins.
    Fix ERC errors.
2026-02-28 Fix Export job name.
2026-02-28 Update TODO list
2026-03-11 Use my fork of sparkengineering kicad-action.
2026-03-11 Do not use kimcp by default with agent.
2026-03-11 Add CPL to export CI files.
2026-03-11 Add a BOM preset and set it in CI.
2026-03-11 Add a part number for USB port
2026-03-14 Minor fixes
2026-03-14 Fix AI.
    Update codex version.
    Introduce SKILLS usage: mount skills at the good location.
    Use default codex_config.toml for now.
    Auto-login, auth.json not committed.
2026-03-14 Update schematics symbols fields for manufactrurer
    Update BOM fields.
2026-03-14 Fix some symbols fields.
2026-03-14 Fix ERC error
2026-03-14 Normalize Vishay manufacturer (delete sub-brand)
2026-03-14 Remove typos and legacy fields
2026-03-14 Add a lot of TestPoints
    Move P-FET at the edge of board.
2026-03-14 Add MPN and stuff to TPS25940
2026-03-14 Add distributor link for battery pack.
2026-03-14 Resolv DRC warnings.
2026-03-14 Fix a wrong capa and add MPN and stuff to STUSB4500
2026-03-14 Improve BOM: exclude uneeded parts, add some columns.
2026-03-14 Mark through-hole component "Do not place" in schematics.
2026-03-14 Fix DRC
2026-03-14 Install kicad-sch-api MCP server.
    Update parsing-kicad-schematics skill.
2026-03-14 Fix wrong footprint (C_0603 instead of R_0603)
